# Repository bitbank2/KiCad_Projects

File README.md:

A collection of KiCad PCB projects. I've included the Gerber files (zipped) so that you can directly order these PCBs from your favorite PCB supplier without having to use KiCad.<br>

# DS3231 Plus 

A DS3231 realtime clock breakout board modelled after the RPI RTC boards. The 5 pin header matches the pinout of the Raspberry Pi and adds the interrupt pin (pulled up to 3.3v). It includes a QWIIC connector (JST 4-pin 1mm) and I also added a small switch to completely disconnect the backup battery if you plan on leaving it unused for an extended period of time. There's a small CR44 backup battery soldered to the back side.<br>
<br>
<br>
<br>

# LCD_64x32_Breakout

A tiny breakout board to make it easier to work with the tiny ST7567 32x64 monochrome LCD display. There's nothing really unique about this board, but it certainly makes it easier to work with LCD panels that use flex cables with odd pin spacing (0.6mm in this case). The 8-pin header order was chosen to match the very popular 'blue' LCDs sold by several vendors in China.<br>

<br>
<br>
<br>
<br>
<br>
<br>

# LCD_HAT

A breakout board to make it easier to connect either a Feather or Nano to the popular 'blue' LCDs available from several vendors in China. These LCDs range from a tiny 0.85" 128x128 ST7735 to a 3.5" 320x480 ILI9488. The PCB also offers a QWIIC I2C connector, 2 momentary push buttons and male 2-pin headers for measuring the power consumption of the QWIIC device or the LCD.<br>

<br>
<br>
<br>
<br>

# RV-3032-C7 RTC Breakout

A breakout board modelled after the RPI RTC boards. The 5 pin header matches the pinout of the RPI and adds the interrupt pin (pulled up to 3.3v). It includes a QWIIC connector (JST 4-pin 1mm), and a pad for the CLKOUT signal. There's a small CR44 backup battery on the back. The RV3032 is similar to the DS3231 in that it's a temperature adjusted (very accurate) clock, but it's much smaller, much lower power and about the same price.<br>
<br>

# Xiao Sharp Memory LCD Breakout

A breakout board for QT Py / Xiao MCU boards to easily control Sharp Memory LCDs. These LCDs require a square wave input to balance the charge; this is provided by the onboard RV3032 RTC. It also includes 2 pushbuttons and a QWIIC I2C connector.<br>
<br>
<br>

# Xiao LCD HAT

A breakout board for QT Py / Xiao MCU boards to easily connect SSD1306 OLEDs and 'blue' 7/8-pin LCD breakout boards. It also includes 2 pushbuttons and a QWIIC I2C connector.<br>
<br>
<br>
<br>

# Sharp Feather/Nano breakout

A breakout board for Feather and Nano MCU boards to easily connect Sharp Memory LCDs. It also includes a RV3032 RTC to drive the VCOM signal of the LCD and act as a low power+reliable realtime clock, 2 pushbuttons and a QWIIC I2C connector.<br>
<br>
<br>
<br>
<br>
<br>
<br>

# CH32V003 (QFN20) breakout

A breakout board for the WCH CH32V003 RISC-V MCU. This breakout is for the QFN20 version of the chip. I've made the QFN20 footprint easier to hand solder by reducing the size of the center ground pad. This leaves a bit more gap to the pins. I solder them without a stencil by mixing the solder paste with a little extra flux to avoid shorts under the chip body.<br>

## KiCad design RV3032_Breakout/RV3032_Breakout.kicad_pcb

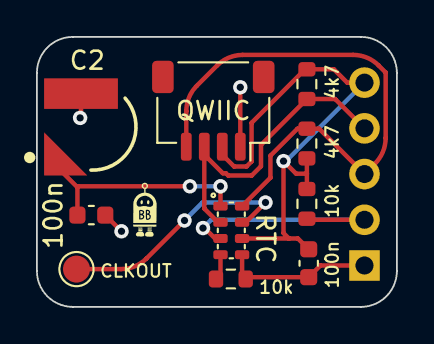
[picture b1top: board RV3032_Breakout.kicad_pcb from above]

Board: 2 copper layers, 20.0 x 15.0 mm, 11 parts (1 on the bottom side), 8 nets.

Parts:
100n: 100n; C_0603_1608Metric
C1: 100n; C_0603_1608Metric
C2: XH414HG-IV01E; CAP_XH414HG-IV01E
CLKOUT: TestPoint; TestPoint_Pad_D1.5mm
J2: Conn_01x05_Female; PinSocket_1x05_P2.54mm_Vertical
QWIIC: Conn_01x04_Female; JST_SH_SM04B-SRSS-TB_1x04-1MP_P1.00mm_Horizontal
R1, R2: 4k7; R_0603_1608Metric
R3, R4: 10k; R_0603_1608Metric
RTC: RV_3032_C7

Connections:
+3.3V: C1.1, J2.5, QWIIC.2, R1.1, R2.1, R3.1, RTC.6 (VCC)
/INT: J2.2, R3.2, RTC.3 (INT)
/SCL: J2.3, QWIIC.4, R2.2, RTC.8 (SCL)
/SDA: J2.4, QWIIC.3, R1.2, RTC.2 (SDA)
GND: 100n.2, C1.2, C2.2, J2.1, QWIIC.1, R4.2, RTC.5 (GND)
unnamed: CLKOUT.1, RTC.7 (CLKOUT)
unnamed: R4.1, RTC.4 (EVI)
unnamed: 100n.1, C2.1, RTC.1 (VBACKUP)

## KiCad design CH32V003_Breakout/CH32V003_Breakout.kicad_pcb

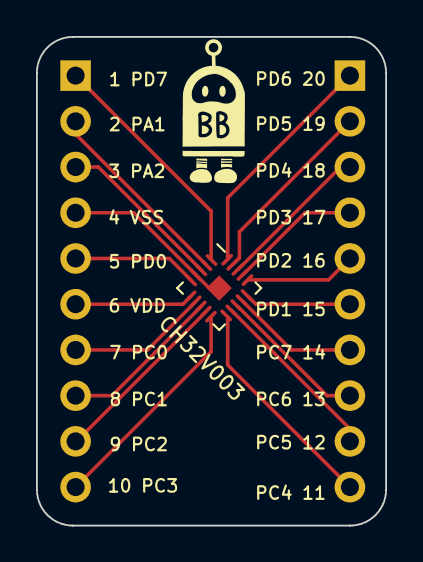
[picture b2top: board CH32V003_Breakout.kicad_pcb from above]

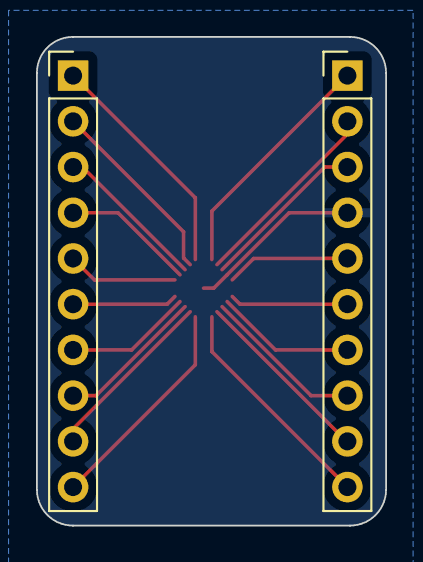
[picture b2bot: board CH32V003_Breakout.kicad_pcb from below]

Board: 2 copper layers, 19.4 x 27.2 mm, 3 parts (2 on the bottom side), 20 nets.

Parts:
CH32V003: QFN-20_3x3_improved
J1, J2: Conn_01x10_Pin; PinHeader_1x10_P2.54mm_Vertical

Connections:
GND: CH32V003.4 (VSS), CH32V003.21 (VSS), J1.4
unnamed: CH32V003.2 (PA1), J1.2
unnamed: CH32V003.3 (PA2), J1.3
unnamed: CH32V003.7 (PC0), J1.7
unnamed: CH32V003.8 (PC1/SDA), J1.8
unnamed: CH32V003.9 (PC2/SCL), J1.9
unnamed: CH32V003.10 (PC3), J1.10
unnamed: CH32V003.11 (PC4), J2.10
unnamed: CH32V003.12 (PC5/SCK/SCL), J2.9
unnamed: CH32V003.13 (PC6/MOSI/SDA), J2.8
unnamed: CH32V003.14 (PC7/MISO), J2.7
unnamed: CH32V003.5 (PD0), J1.5
unnamed: CH32V003.15 (PD1/SWIO), J2.6
unnamed: CH32V003.16 (PD2), J2.5
unnamed: CH32V003.17 (PD3), J2.4
unnamed: CH32V003.18 (PD4), J2.3
unnamed: CH32V003.19 (PD5), J2.2
unnamed: CH32V003.20 (PD6), J2.1
unnamed: CH32V003.1 (PD7), J1.1
unnamed: CH32V003.6 (VDD), J1.6

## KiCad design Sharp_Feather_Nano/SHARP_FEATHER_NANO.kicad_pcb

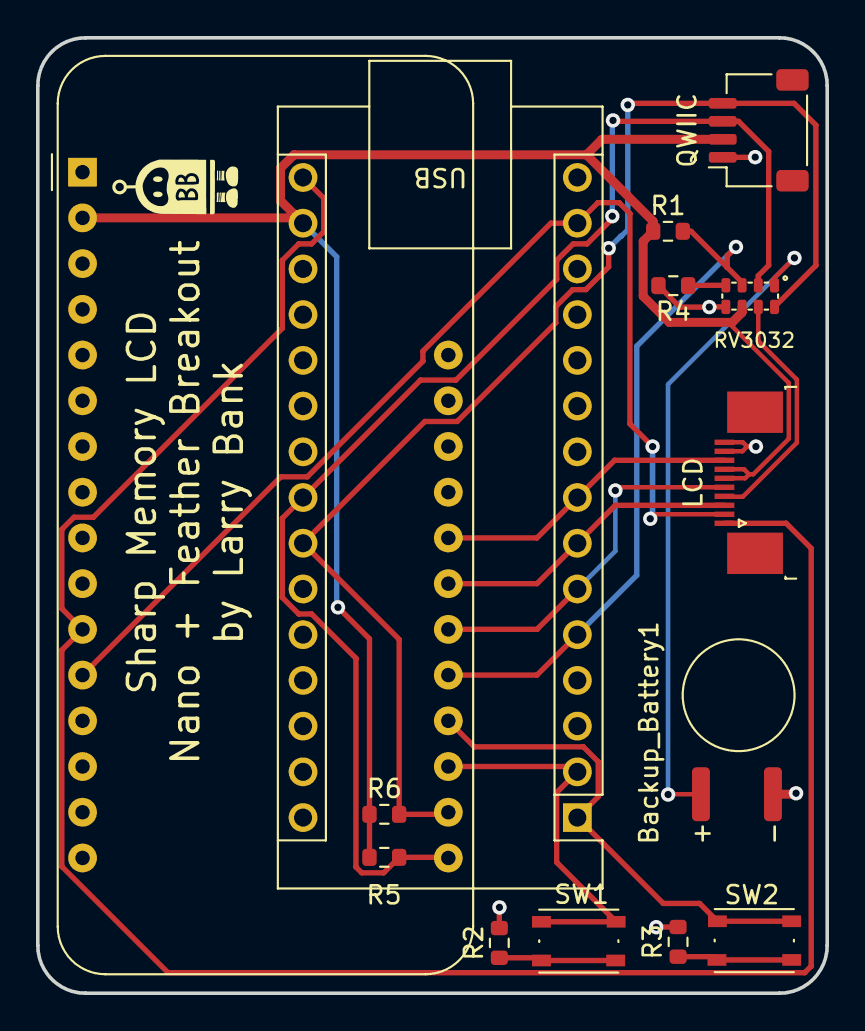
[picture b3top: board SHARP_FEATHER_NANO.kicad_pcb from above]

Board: 2 copper layers, 43.9 x 53.1 mm, 14 parts (0 on the bottom side), 17 nets.

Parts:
A1: Arduino_Nano_v3.x; Arduino_Nano
A2: Adafruit_Feather_Generic; Adafruit_Feather
Backup_Battery1: Battery_Cell; CR44_Tabs
LCD: TE_1-1734839-0_1x10-1MP_P0.5mm_Horizontal
QWIIC: QWIIC; JST_SH_SM04B-SRSS-TB_1x04-1MP_P1.00mm_Horizontal
R1: 100K; R_0603_1608Metric
R2, R3: 10k; R_0603_1608Metric
R4: 10K; R_0603_1608Metric
R5, R6: 4.7k; R_0603_1608Metric
RV1: RV_3032_C7
SW1, SW2: SW_Push; SW_Push_1P1T_NO_Vertical_Wuerth_434133025816

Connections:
+3.3V: A1.17 (3V3), A2.2 (3V3), LCD.6 (VDDA), LCD.7 (VDD), QWIIC.2, R1.1, R5.1, R6.1, RV1.6 (VCC)
BUTTON0: A1.2 (D0/RX), A2.19 (D0), SW1.1
BUTTON1: A1.1 (D1/TX), A2.20 (D1), SW2.2
CLKOUT: LCD.4 (EXTCOMIN), RV1.7 (CLKOUT)
CS: A1.7 (D4), A2.23 (D4), LCD.3 (CS)
DISPON: A1.6 (D3), A2.22 (D3), LCD.5 (DISP_ON)
EXTMODE: A1.8 (D5), A2.24 (D5), LCD.8 (EXTMODE)
GND: A1.4 (GND), A1.29 (GND), A2.4 (GND), Backup_Battery1.2 (-), LCD.9 (VSS), LCD.10 (VSSA), QWIIC.1, R2.2, R3.2, R4.2, RV1.5 (GND)
INT: A1.5 (D2), A2.21 (D2), R1.2, RV1.3 (INT)
MOSI: A1.14 (D11), A2.12 (MOSI), LCD.2 (SDA)
unnamed: R2.1, SW1.2
unnamed: R3.1, SW2.1
unnamed: R4.1, RV1.4 (EVI)
SCK: A1.16 (D13), A2.11 (SCK), LCD.1 (SCL)
SCL: A1.24 (A5), A2.18 (SCL), QWIIC.4, R6.2, RV1.8 (SCL)
SDA: A1.23 (A4), A2.17 (SDA), QWIIC.3, R5.2, RV1.2 (SDA)
VBATT: Backup_Battery1.1 (+), RV1.1 (VBACKUP)

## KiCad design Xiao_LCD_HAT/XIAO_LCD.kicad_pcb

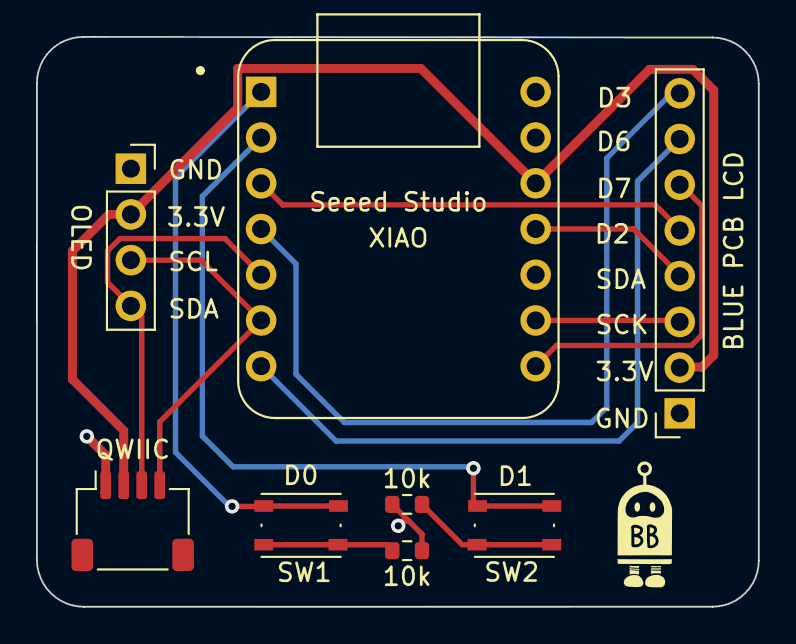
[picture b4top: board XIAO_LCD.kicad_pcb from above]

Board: 2 copper layers, 40.1 x 31.7 mm, 8 parts (0 on the bottom side), 14 nets.

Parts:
J1: OLED; PinSocket_1x04_P2.54mm_Vertical
J3: BLUE PCB LCD; PinSocket_1x08_P2.54mm_Vertical
QWIIC: QWIIC; JST_SH_SM04B-SRSS-TB_1x04-1MP_P1.00mm_Horizontal
R1, R2: 10k; R_0603_1608Metric
SW1, SW2: SW_Push; SW_Push_1P1T_NO_Vertical_Wuerth_434133025816
U1: SeeeduinoXIAO; XIAO-Generic-Thruhole-14P-2.54-21X17.8MM

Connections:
+3.3V: J1.2, J3.2, QWIIC.2, U1.12 (3V3)
BUTTON0: SW1.1, U1.1 (PA02_A0_D0)
BUTTON1: SW2.2, U1.2 (PA4_A1_D1)
GND: J1.1, J3.1, QWIIC.1, R1.2, R2.2, U1.13 (GND)
unnamed: J3.3, U1.9 (PA7_A8_D8_SCK)
unnamed: J3.4, U1.11 (PA6_A10_D10_MOSI)
unnamed: J3.5, U1.3 (PA10_A2_D2)
unnamed: J3.6, U1.8 (PB09_A7_D7_RX)
unnamed: J3.7, U1.7 (PB08_A6_D6_TX)
unnamed: J3.8, U1.4 (PA11_A3_D3)
unnamed: R1.1, SW1.2
unnamed: R2.1, SW2.1
SCL: J1.3, QWIIC.4, U1.6 (PA9_A5_D5_SCL)
SDA: J1.4, QWIIC.3, U1.5 (PA8_A4_D4_SDA)

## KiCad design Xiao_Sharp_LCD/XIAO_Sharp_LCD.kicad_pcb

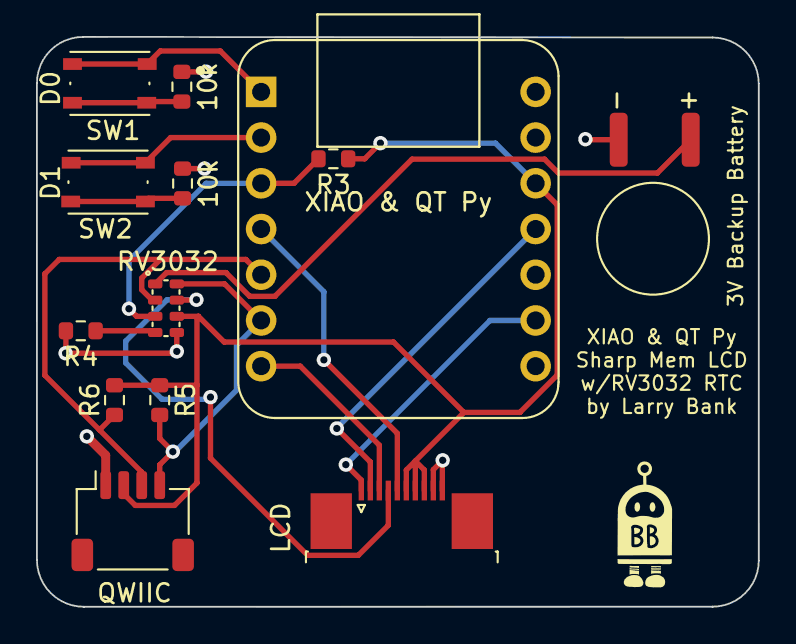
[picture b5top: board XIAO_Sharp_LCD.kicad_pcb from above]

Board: 2 copper layers, 40.1 x 31.7 mm, 13 parts (0 on the bottom side), 16 nets.

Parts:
3V Backup Battery: Battery_Cell; CR44_Tabs
LCD: TE_1-1734839-0_1x10-1MP_P0.5mm_Horizontal
QWIIC: QWIIC; JST_SH_SM04B-SRSS-TB_1x04-1MP_P1.00mm_Horizontal
R1, R2: 10k; R_0603_1608Metric
R3: 100K; R_0603_1608Metric
R4: 10K; R_0603_1608Metric
R5, R6: 4.7K; R_0603_1608Metric
RV3032: RV_3032_C7
SW1, SW2: SW_Push; SW_Push_1P1T_NO_Vertical_Wuerth_434133025816
U1: SeeeduinoXIAO; XIAO-Generic-Thruhole-14P-2.54-21X17.8MM

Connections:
+3.3V: LCD.6 (VDDA), LCD.7 (VDD), LCD.8 (EXTMODE), QWIIC.2, R3.1, R5.1, R6.1, RV3032.6 (VCC), U1.12 (3V3)
BUTTON0: SW1.1, U1.1 (PA02_A0_D0)
BUTTON1: SW2.2, U1.2 (PA4_A1_D1)
CLKOUT: LCD.4 (EXTCOMIN), RV3032.7 (CLKOUT)
GND: 3V Backup Battery.2 (-), LCD.9 (VSS), LCD.10 (VSSA), QWIIC.1, R1.2, R2.2, R4.2, RV3032.5 (GND), U1.13 (GND)
INT: R3.2, RV3032.3 (INT), U1.3 (PA10_A2_D2)
unnamed: R1.1, SW1.2
unnamed: R2.1, SW2.1
unnamed: R4.1, RV3032.4 (EVI)
unnamed: LCD.2 (SDA), U1.11 (PA6_A10_D10_MOSI)
unnamed: LCD.1 (SCL), U1.9 (PA7_A8_D8_SCK)
unnamed: LCD.5 (DISP_ON), U1.4 (PA11_A3_D3)
unnamed: LCD.3 (CS), U1.7 (PB08_A6_D6_TX)
SCL: QWIIC.4, R5.2, RV3032.8 (SCL), U1.6 (PA9_A5_D5_SCL)
SDA: QWIIC.3, R6.2, RV3032.2 (SDA), U1.5 (PA8_A4_D4_SDA)
VBATT: 3V Backup Battery.1 (+), RV3032.1 (VBACKUP)

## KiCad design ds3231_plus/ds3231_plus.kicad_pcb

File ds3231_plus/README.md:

DS3231_PLUS<br>
-----------------------------------
Copyright (c) 2023 BitBank Software, Inc.<br>
bitbank@pobox.com<br>
<br>
A simple DS3231 RTC breakout board. It includes a 5 pin 0.1" header matched to the Raspberry Pi 40 pin header. The "++" refers to the added feature of having the IRQ pin broken out to a pin that was unused on similar breakouts. I also added a Qwiic I2C connector and backup battery cutoff switch. I wanted the switch because I've left these devices in a drawer before without proper shutdown and the battery will run down. By the time you're ready to use them, the battery is dead. 
<br>
<br>

<br>

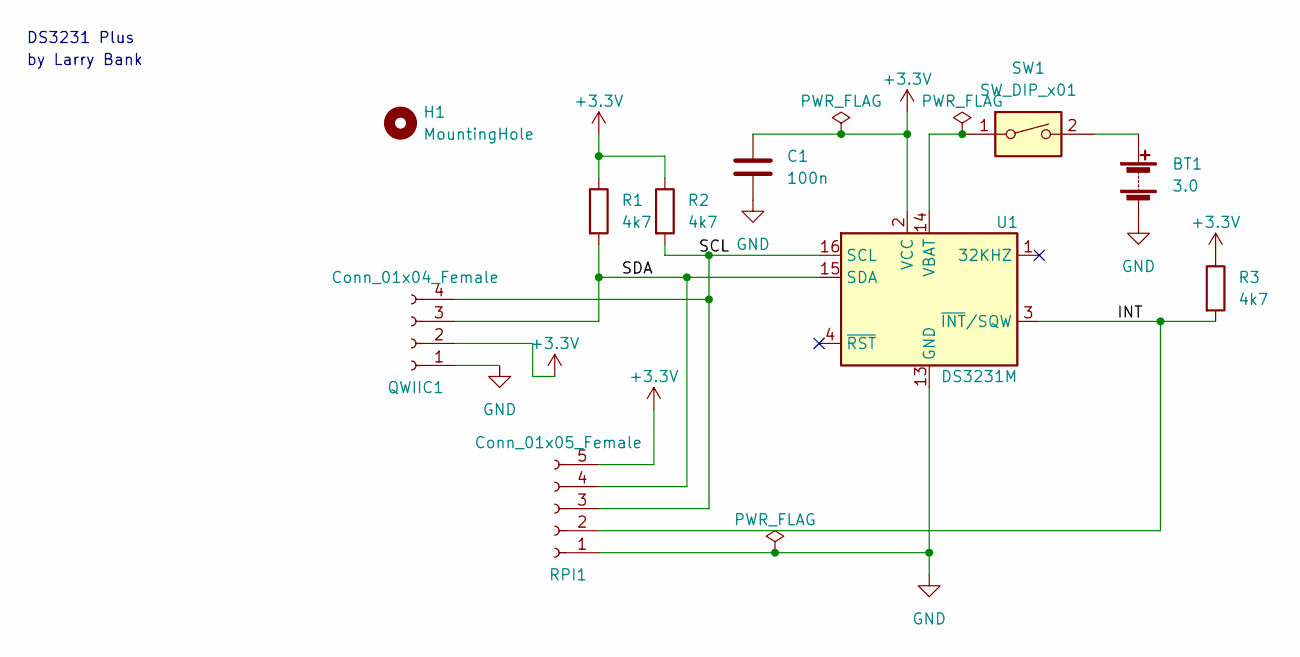
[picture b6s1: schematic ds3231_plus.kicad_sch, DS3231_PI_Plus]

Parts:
BT1: 3.0; CR44_Tabs
C1: 100n; C_0603_1608Metric
H1: MountingHole; MountingHole_2.1mm
QWIIC1: Conn_01x04_Female; JST_SH_SM04B-SRSS-TB_1x04-1MP_P1.00mm_Horizontal
R1, R2, R3: 4k7; R_0603_1608Metric
RPI1: Conn_01x05_Female; PinSocket_1x05_P2.54mm_Vertical
SW1: SW_DIP_x01; SW_DIP_SPSTx01_Slide_Copal_CHS-01B_W7.62mm_P1.27mm
U1: DS3231M; SOIC-16W_7.5x10.3mm_P1.27mm

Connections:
+3.3V: C1.1, QWIIC1.2, R1.1, R2.1, R3.1, RPI1.5, U1.2 (VCC); also elsewhere on the board
/INT: R3.2, RPI1.2, U1.3 (~INT/SQW)
/SCL: QWIIC1.4, R2.2, RPI1.3, U1.16 (SCL); also elsewhere on the board
/SDA: QWIIC1.3, R1.2, RPI1.4, U1.15 (SDA); also elsewhere on the board
GND: BT1.2 (-), C1.2, QWIIC1.1, RPI1.1, U1.5 (GND), U1.6 (GND), U1.7 (GND), U1.8 (GND), U1.9 (GND), U1.10 (GND), U1.11 (GND), U1.12 (GND), U1.13 (GND); also elsewhere on the board
unnamed: SW1.1, U1.14 (VBAT)
unnamed: BT1.1 (+), SW1.2

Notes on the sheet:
DS3231 Plus
by Larry Bank

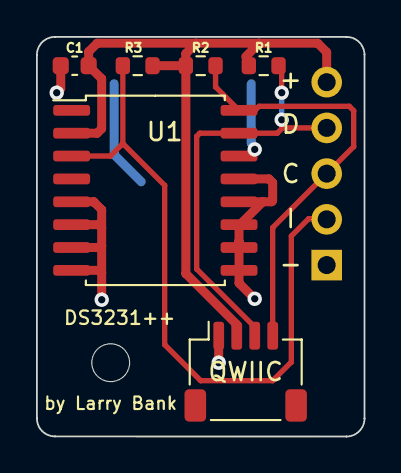
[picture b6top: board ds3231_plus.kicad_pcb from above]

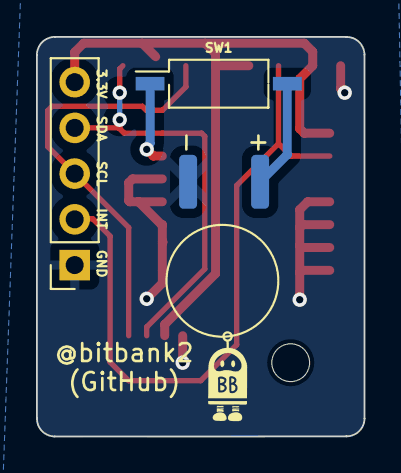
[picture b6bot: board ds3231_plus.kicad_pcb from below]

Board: 2 copper layers, 18.2 x 22.2 mm, 10 parts (3 on the bottom side), 7 nets.

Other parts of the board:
QWIIC: Conn_01x04_Female; JST_SH_SM04B-SRSS-TB_1x04-1MP_P1.00mm_Horizontal

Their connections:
+3.3V: QWIIC.2; also elsewhere on the board
/SCL: QWIIC.4; also elsewhere on the board
/SDA: QWIIC.3; also elsewhere on the board
GND: QWIIC.1; also elsewhere on the board

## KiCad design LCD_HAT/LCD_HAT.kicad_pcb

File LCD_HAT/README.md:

LCD_HAT<br>
-----------------------------------
Copyright (c) 2023 BitBank Software, Inc.<br>
bitbank@pobox.com<br>
<br>
A simple PCB to easily connect LCD breakout boards to Arduino Nano or Feather MCU boards. Includes 2 momentary push buttons and Qwiic I2C connector. The GPIOs used for the LCD connection are marked next to the female header. Likewise the buttons.
<br>
This photo shows an Arduino Nano RP2040 Connect and UnexpectedMaker FeatherS3 both using the same board and 2 types of LCDs supported with this pinout:
<br>
<br>

<br>

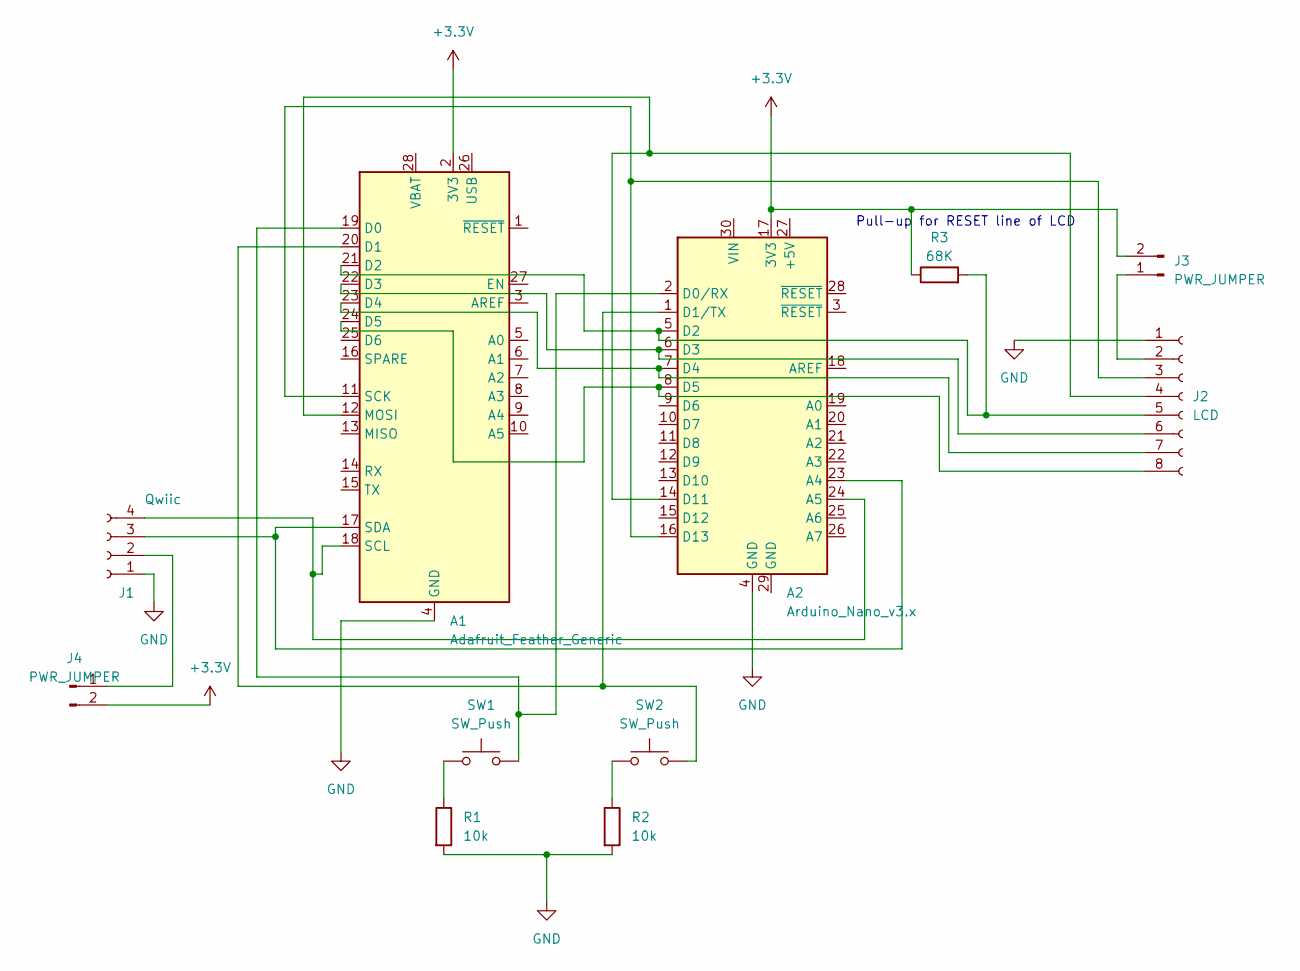
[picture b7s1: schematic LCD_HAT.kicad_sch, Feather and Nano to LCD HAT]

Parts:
A1: Adafruit_Feather_Generic; Adafruit_Feather
A2: Arduino_Nano_v3.x; Arduino_Nano
J1: Qwiic; JST_SH_SM04B-SRSS-TB_1x04-1MP_P1.00mm_Horizontal
J2: LCD; PinSocket_1x08_P2.54mm_Vertical
J3, J4: PWR_JUMPER; PinHeader_1x02_P2.54mm_Vertical
R1, R2: 10k; R_0603_1608Metric
R3: 68K; R_0603_1608Metric
SW1, SW2: SW_Push; SW_Push_1P1T_NO_Vertical_Wuerth_434133025816

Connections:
+3.3V: A1.2 (3V3), A2.17 (3V3), J3.2, J4.2, R3.1
GND: A1.4 (GND), A2.4 (GND), J1.1, J2.1, R1.2, R2.2
unnamed: A1.19 (D0), A2.2 (D0/RX), SW1.2
unnamed: A1.20 (D1), A2.1 (D1/TX), SW2.2
unnamed: A1.21 (D2), A2.5 (D2), J2.5, R3.2
unnamed: A1.22 (D3), A2.6 (D3), J2.6
unnamed: A1.23 (D4), A2.7 (D4), J2.7
unnamed: A1.24 (D5), A2.8 (D5), J2.8
unnamed: A1.12 (MOSI), A2.14 (D11), J2.4
unnamed: A1.11 (SCK), A2.16 (D13), J2.3
unnamed: A1.18 (SCL), A2.24 (A5), J1.4
unnamed: A1.17 (SDA), A2.23 (A4), J1.3
unnamed: J1.2, J4.1
unnamed: J2.2, J3.1
unnamed: R1.1, SW1.1
unnamed: R2.1, SW2.1

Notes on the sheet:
Pull-up for RESET line of LCD

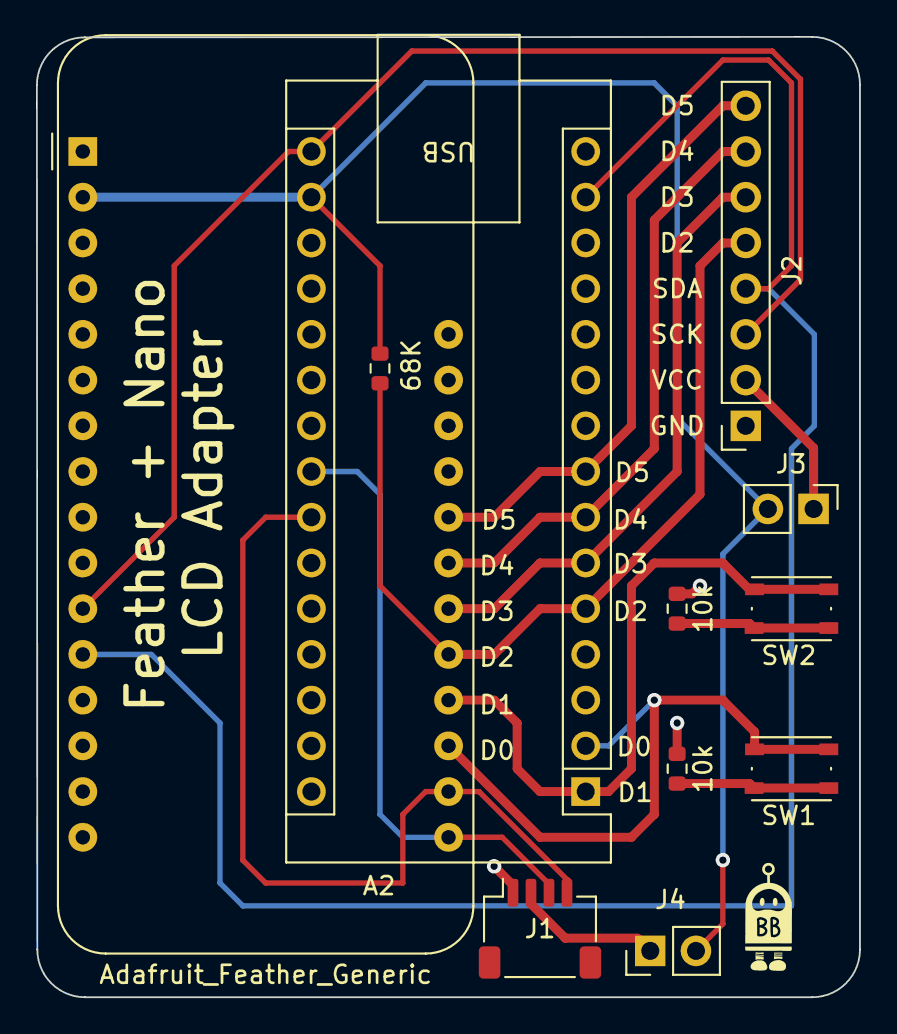
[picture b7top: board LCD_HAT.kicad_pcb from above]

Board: 2 copper layers, 45.7 x 53.4 mm, 11 parts (0 on the bottom side), 16 nets.

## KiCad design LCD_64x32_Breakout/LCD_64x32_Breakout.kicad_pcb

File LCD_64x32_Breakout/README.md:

LCD_64x32_Breakout<br>
-----------------------------------
Copyright (c) 2023 BitBank Software, Inc.<br>
bitbank@pobox.com<br>
<br>
A PCB to provide a simpler 0.1" header to the tiny ST7567 32x64 monochrome LCD. The pinout matches a lot of popular "blue" PCB breakout boards sold on AliExpress. It can be soldered with a small tip soldering iron, but would be easier to do with a hot air gun.
<br>
The image shows the 3D render from KiCad of the front ant back.
<br>
<br>

<br>
Here's an earlier version of the board connected to the LCD<br>
<br>

<br>

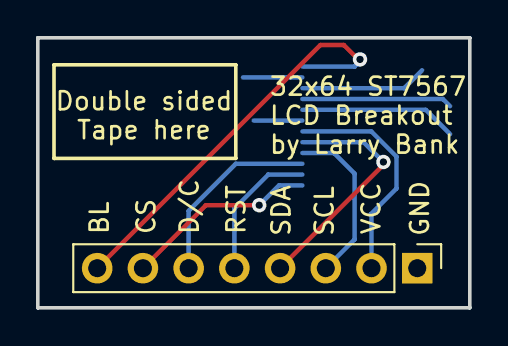
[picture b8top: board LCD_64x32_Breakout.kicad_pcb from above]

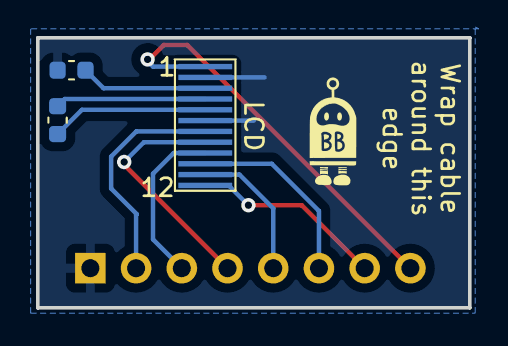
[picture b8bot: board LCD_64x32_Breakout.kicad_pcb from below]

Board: 2 copper layers, 24.0 x 15.0 mm, 4 parts (3 on the bottom side), 11 nets.

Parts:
C1, C2: 1uF; C_0603_1608Metric
J1: Conn_01x08_Pin; PinHeader_1x08_P2.54mm_Vertical
LCD: FPC_12x0.6

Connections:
GND: C1.1, J1.1, LCD.2 (LEDK), LCD.6 (VSS)
unnamed: J1.2, LCD.7 (VDD)
unnamed: J1.3, LCD.9 (SCK)
unnamed: J1.4, LCD.8 (SDA)
unnamed: J1.5, LCD.11 (RST)
unnamed: J1.6, LCD.10 (DC)
unnamed: J1.7, LCD.12 (CS)
unnamed: J1.8, LCD.1 (LEDA)
unnamed: C2.2, LCD.4 (VB1+)
unnamed: C2.1, LCD.5 (VB1-)
unnamed: C1.2, LCD.3 (VLCD)

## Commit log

2023-02-08 Added LCD_HAT project
2023-03-04 Added readme and photo
2023-03-04 Added readme to ds3231_plus
2023-03-04 fixed readme
2023-03-27 Added 64x32 ST7567 LCD breakout
2023-03-27 Added photo
2023-06-08 Added ds3231 image
2023-06-08 Added jpeg
2023-06-08 changed readme
2023-06-08 Update README.md
    Added first 3D render image + description
2023-06-08 Added 32x64 LCD breakout to readme
2023-06-08 Added lcd_hat image
2023-06-08 Update README.md
    fixed alignment
2023-06-08 Updated project files
2023-06-08 Added RV3032
2023-06-12 Added Xiao Sharp LCD project
2023-06-12 Updated README for Xiao Sharp LCD
2023-06-16 Added XIAO_LCD_HAT
2023-06-20 Added schematic drawings
2023-07-06 Added Sharp_Feather_Nano PCB
2023-10-21 Added CH32V003 Breakout
2023-10-21 Update README.md
    fixed formatting
2024-09-22 Updated to use supercap instead of battery
